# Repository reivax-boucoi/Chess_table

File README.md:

# Chess_table
Automated chess table with magnets &amp; CoreXY

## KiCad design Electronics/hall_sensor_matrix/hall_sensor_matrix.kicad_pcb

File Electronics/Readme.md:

# CNC Controller

### GRBL based controller running on Atmega328p and using A4988 stepper drivers.

Even though the chess board only requires 2 axis of motion (corexy platform), board has been developped with full 3 axis features.

Coolant, spindle, ... are brought out as 12V low-side switches (0.5A/1A). This is used to activate the electromagnet for the head.

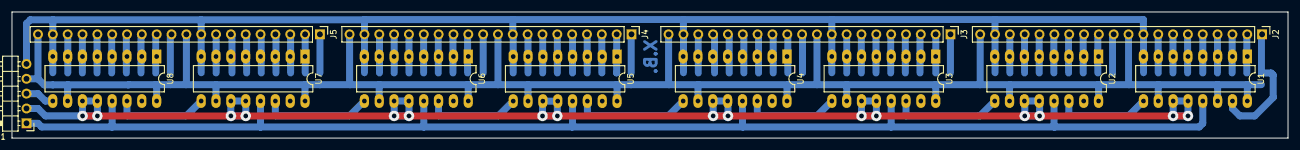
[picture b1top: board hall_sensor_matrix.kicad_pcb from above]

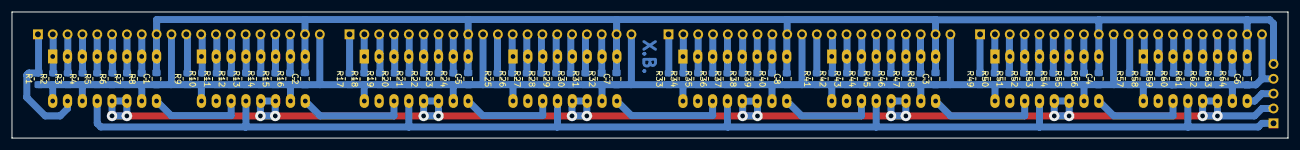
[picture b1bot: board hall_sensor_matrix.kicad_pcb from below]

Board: 2 copper layers, 218.4 x 21.6 mm, 85 parts (72 on the bottom side), 76 nets.

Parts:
C1, C2, C3, C4, C5, C6, C7: 100n; C_0805_2012Metric_Pad1.18x1.45mm_HandSolder
C8: 100n; R_0805_2012Metric_Pad1.20x1.40mm_HandSolder
J1: Conn_01x05; PinHeader_1x05_P2.54mm_Horizontal
J2, J3, J4, J5: Conn_01x20; PinHeader_1x20_P2.54mm_Vertical
R1, R2, R3, R4, R5, R6, R7, R8, R9, R10, R11, R12, R13, R14, R15, R16, R17, R18, R19, R20, R21, R22, R23, R24, R25, R26, R27, R28, R29, R30, R31, R32, R33, R34, R35, R36, R37, R38, R39, R40, R41, R42, R43, R44, R45, R46, R47, R48, R49, R50, R51, R52, R53, R54, R55, R56, R57, R58, R59, R60, R61, R62, R63, R64: R; R_0805_2012Metric_Pad1.20x1.40mm_HandSolder
U1, U2, U3, U4, U5, U6, U7, U8: 74LS597; DIP-16_W7.62mm_LongPads

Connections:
+5V: C1.1, C2.1, C3.1, C4.1, C5.1, C6.1, C7.1, C8.1, J1.4, J2.10, J2.20, J3.10, J3.20, J4.10, J4.20, J5.10, J5.20, R1.1, R2.1, R3.1, R4.1, R5.1, R6.1, R7.1, R8.1, R9.1, R10.1, R11.1, R12.1, R13.1, R14.1, R15.1, R16.1, R17.1, R18.1, R19.1, R20.1, R21.1, R22.1, R23.1, R24.1, R25.1, R26.1, R27.1, R28.1, R29.1, R30.1, R31.1, R32.1, R33.1, R34.1, R35.1, R36.1, R37.1, R38.1, R39.1, R40.1, R41.1, R42.1, R43.1, R44.1, R45.1, R46.1, R47.1, R48.1, R49.1, R50.1, R51.1, R52.1, R53.1, R54.1, R55.1, R56.1, R57.1, R58.1, R59.1, R60.1, R61.1, R62.1, R63.1, R64.1, U1.10 (~R), U1.14 (SER), U1.16 (VCC), U2.10 (~R), U2.16 (VCC), U3.10 (~R), U3.16 (VCC), U4.10 (~R), U4.16 (VCC), U5.10 (~R), U5.16 (VCC), U6.10 (~R), U6.16 (VCC), U7.10 (~R), U7.16 (VCC), U8.10 (~R), U8.16 (VCC)
/A1: J2.1, R1.2, U1.15 (A)
/A2: J2.2, R2.2, U1.1 (B)
/A3: J2.3, R3.2, U1.2 (C)
/A4: J2.4, R4.2, U1.3 (D)
/A5: J2.5, R5.2, U1.4 (E)
/A6: J2.6, R6.2, U1.5 (F)
/A7: J2.7, R7.2, U1.6 (G)
/A8: J2.8, R8.2, U1.7 (H)
/B1: J2.11, R9.2, U2.15 (A)
/B2: J2.12, R10.2, U2.1 (B)
/B3: J2.13, R11.2, U2.2 (C)
/B4: J2.14, R12.2, U2.3 (D)
/B5: J2.15, R13.2, U2.4 (E)
/B6: J2.16, R14.2, U2.5 (F)
/B7: J2.17, R15.2, U2.6 (G)
/B8: J2.18, R16.2, U2.7 (H)
/C1: J3.1, R17.2, U3.15 (A)
/C2: J3.2, R18.2, U3.1 (B)
/C3: J3.3, R19.2, U3.2 (C)
/C4: J3.4, R20.2, U3.3 (D)
/C5: J3.5, R21.2, U3.4 (E)
/C6: J3.6, R22.2, U3.5 (F)
/C7: J3.7, R23.2, U3.6 (G)
/C8: J3.8, R24.2, U3.7 (H)
/CLK: J1.2, U1.11 (SCK), U1.12 (CLK), U2.11 (SCK), U2.12 (CLK), U3.11 (SCK), U3.12 (CLK), U4.11 (SCK), U4.12 (CLK), U5.11 (SCK), U5.12 (CLK), U6.11 (SCK), U6.12 (CLK), U7.11 (SCK), U7.12 (CLK), U8.11 (SCK), U8.12 (CLK)
/D1: J3.11, R25.2, U4.15 (A)
/D2: J3.12, R26.2, U4.1 (B)
/D3: J3.13, R27.2, U4.2 (C)
/D4: J3.14, R28.2, U4.3 (D)
/D5: J3.15, R29.2, U4.4 (E)
/D6: J3.16, R30.2, U4.5 (F)
/D7: J3.17, R31.2, U4.6 (G)
/D8: J3.18, R32.2, U4.7 (H)
/Dout0: U1.9 (QH), U2.14 (SER)
/Dout1: U2.9 (QH), U3.14 (SER)
/Dout2: U3.9 (QH), U4.14 (SER)
/Dout3: U4.9 (QH), U5.14 (SER)
/Dout4: U5.9 (QH), U6.14 (SER)
/Dout5: U6.9 (QH), U7.14 (SER)
/Dout6: U7.9 (QH), U8.14 (SER)
/Dout7: J1.3, U8.9 (QH)
/E1: J4.1, R33.2, U5.15 (A)
/E2: J4.2, R34.2, U5.1 (B)
/E3: J4.3, R35.2, U5.2 (C)
/E4: J4.4, R36.2, U5.3 (D)
/E5: J4.5, R37.2, U5.4 (E)
/E6: J4.6, R38.2, U5.5 (F)
/E7: J4.7, R39.2, U5.6 (G)
/E8: J4.8, R40.2, U5.7 (H)
/F1: J4.11, R41.2, U6.15 (A)
/F2: J4.12, R42.2, U6.1 (B)
/F3: J4.13, R43.2, U6.2 (C)
/F4: J4.14, R44.2, U6.3 (D)
/F5: J4.15, R45.2, U6.4 (E)
/F6: J4.16, R46.2, U6.5 (F)
/F7: J4.17, R47.2, U6.6 (G)
/F8: J4.18, R48.2, U6.7 (H)
/G1: J5.1, R49.2, U7.15 (A)
/G2: J5.2, R50.2, U7.1 (B)
/G3: J5.3, R51.2, U7.2 (C)
/G4: J5.4, R52.2, U7.3 (D)
/G5: J5.5, R53.2, U7.4 (E)
/G6: J5.6, R54.2, U7.5 (F)
/G7: J5.7, R55.2, U7.6 (G)
/G8: J5.8, R56.2, U7.7 (H)
/H1: J5.11, R57.2, U8.15 (A)
/H2: J5.12, R58.2, U8.1 (B)
/H3: J5.13, R59.2, U8.2 (C)
/H4: J5.14, R60.2, U8.3 (D)
/H5: J5.15, R61.2, U8.4 (E)
/H6: J5.16, R62.2, U8.5 (F)
/H7: J5.17, R63.2, U8.6 (G)
/H8: J5.18, R64.2, U8.7 (H)
/Latch: J1.1, U1.13 (~SLoad), U2.13 (~SLoad), U3.13 (~SLoad), U4.13 (~SLoad), U5.13 (~SLoad), U6.13 (~SLoad), U7.13 (~SLoad), U8.13 (~SLoad)
GND: C1.2, C2.2, C3.2, C4.2, C5.2, C6.2, C7.2, C8.2, J1.5, J2.9, J2.19, J3.9, J3.19, J4.9, J4.19, J5.9, J5.19, U1.8 (GND), U2.8 (GND), U3.8 (GND), U4.8 (GND), U5.8 (GND), U6.8 (GND), U7.8 (GND), U8.8 (GND)

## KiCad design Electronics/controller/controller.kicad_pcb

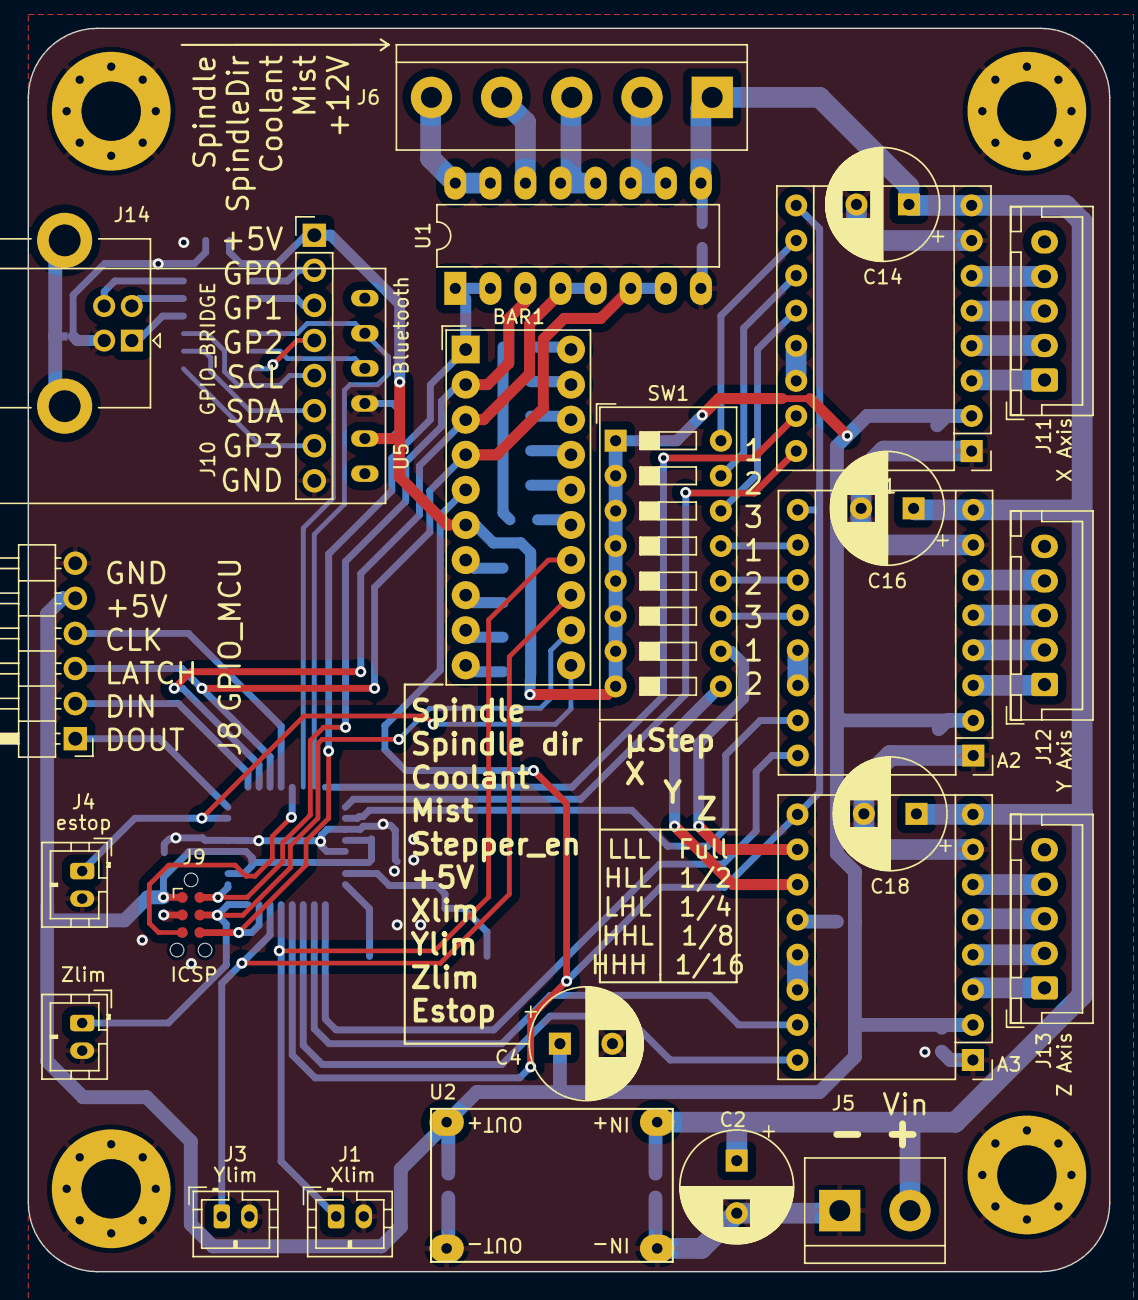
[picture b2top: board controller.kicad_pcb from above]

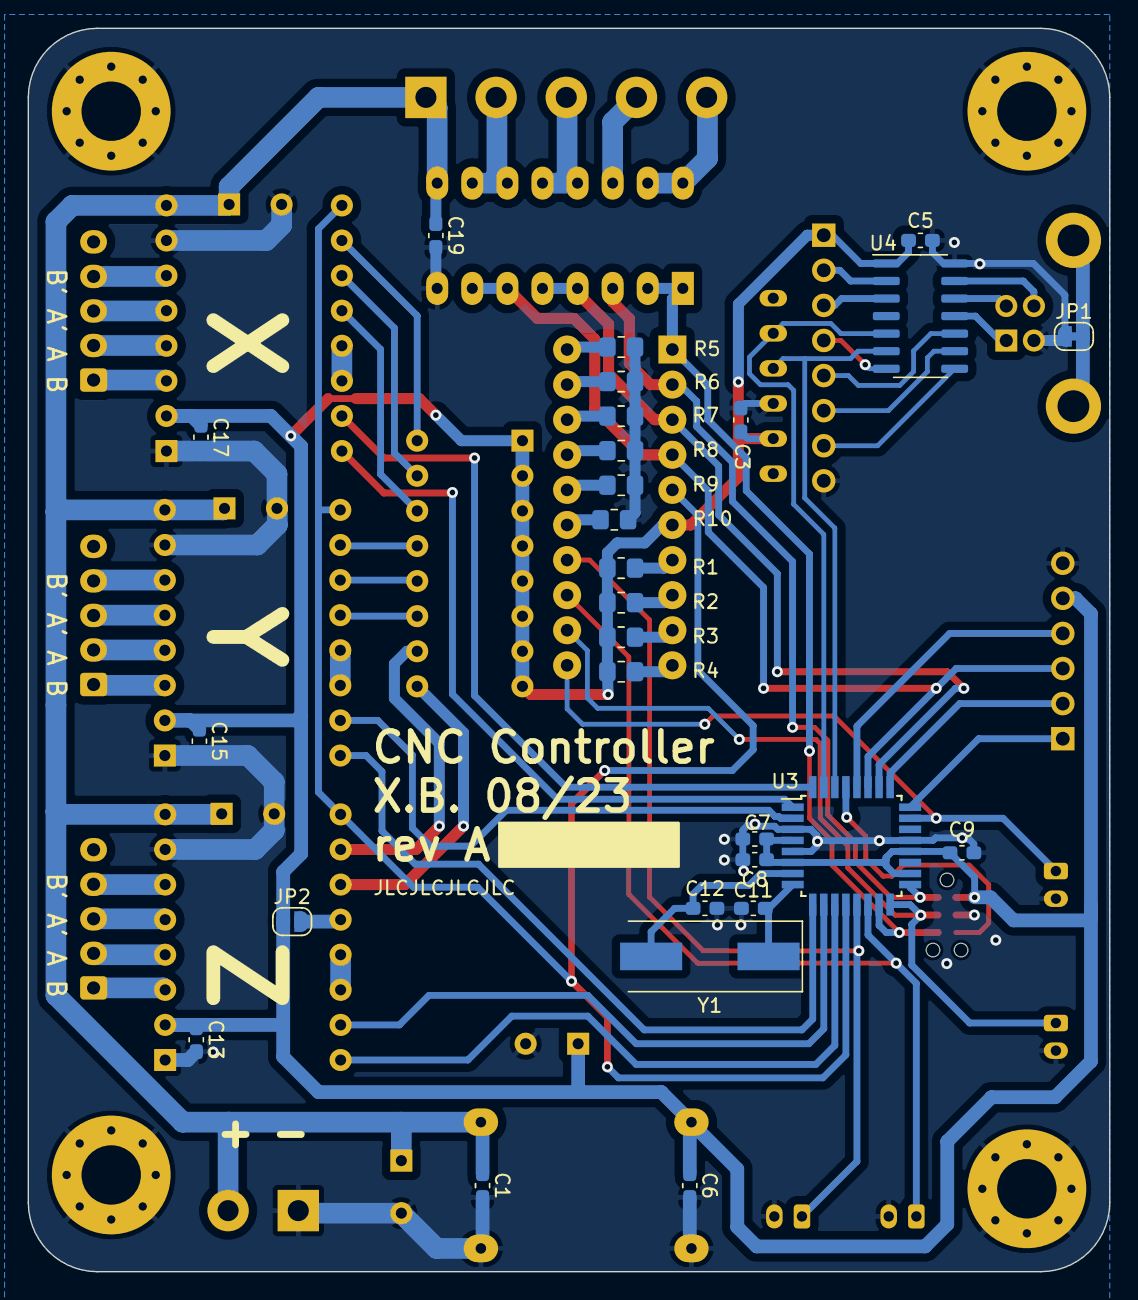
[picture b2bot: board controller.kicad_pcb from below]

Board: 2 copper layers, 78.3 x 90.0 mm, 58 parts (28 on the bottom side), 74 nets.

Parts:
A1, A2, A3: Pololu_Breakout_A4988; Pololu_Breakout-16_15.2x20.3mm
BAR1: HDSP-4830_2; HDSP-4830
C1, C3, C5, C6, C7, C8, C9, C13, C15, C17, C19: 100n; C_0603_1608Metric_Pad1.08x0.95mm_HandSolder
C2, C4, C14, C16, C18: 47u; CP_Radial_D8.0mm_P3.80mm
C11, C12: 22p; C_0603_1608Metric_Pad1.08x0.95mm_HandSolder
H1, H2, H3, H4: MountingHole_Pad; MountingHole_4.3mm_M4_Pad_Via
J1: Xlim; JST_PH_B2B-PH-K_1x02_P2.00mm_Vertical
J2: Zlim; JST_PH_B2B-PH-K_1x02_P2.00mm_Vertical
J3: Ylim; JST_PH_B2B-PH-K_1x02_P2.00mm_Vertical
J4: estop; JST_PH_B2B-PH-K_1x02_P2.00mm_Vertical
J5: Vin; TerminalBlock_bornier-2_P5.08mm
J6: Screw_Terminal_01x05; TerminalBlock_bornier-5_P5.08mm
J8: GPIO_MCU; PinHeader_1x06_P2.54mm_Horizontal
J9: ICSP; Tag-Connect_TC2030-IDC-NL_2x03_P1.27mm_Vertical
J10: GPIO_BRIDGE; PinHeader_1x08_P2.54mm_Vertical
J11: X Axis; JST_XH_B5B-XH-A_1x05_P2.50mm_Vertical
J12: Y Axis; JST_XH_B5B-XH-A_1x05_P2.50mm_Vertical
J13: Z Axis; JST_XH_B5B-XH-A_1x05_P2.50mm_Vertical
J14: USB_A; USB_B_Lumberg_2411_02_Horizontal
JP1: Jumper_2_Bridged; SolderJumper-2_P1.3mm_Bridged_RoundedPad1.0x1.5mm
JP2: Jumper_2_Open; SolderJumper-2_P1.3mm_Open_RoundedPad1.0x1.5mm
R1, R2, R3, R4, R5, R6, R7, R8, R9, R10: 1k; R_0805_2012Metric_Pad1.20x1.40mm_HandSolder
SW1: SW_DIP_x08; SW_DIP_SPSTx08_Slide_9.78x22.5mm_W7.62mm_P2.54mm
U1: ULN2003A; DIP-16_W7.62mm_LongPads
U2: Mini360; Mini360_step-down
U3: ATmega328P-A; TQFP-32_7x7mm_P0.8mm
U4: MCP2221AxSL; SOIC-14_3.9x8.7mm_P1.27mm
U5: Bluetooth; BlueSmirf
Y1: 16MHz; Crystal_SMD_HC49-SD

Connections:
+5V: A1.2 (VDD), A2.2 (VDD), A3.2 (VDD), BAR1.6 (A), C3.1, C4.1, C5.1, C6.1, C7.1, C8.1, C9.1, C13.1, C15.1, C17.1, J8.5, J9.1, J10.1, JP2.1 (A), R1.1, R2.1, R3.1, R4.1, SW1.1, SW1.2, SW1.3, SW1.4, SW1.5, SW1.6, SW1.7, SW1.8, U2.4 (OUT+), U3.4 (VCC), U3.6 (VCC), U3.18 (AVCC), U3.20 (AREF), U4.1 (VDD), U5.2 (VCC)
+12V: A1.8 (VMOT), A2.8 (VMOT), A3.8 (VMOT), C1.1, C2.1, C14.1, C16.1, C18.1, C19.1, J5.2, J6.1, U1.9 (COM), U2.2 (IN+)
/MCU/CLK: J8.4, U3.28 (PC5)
/MCU/DIN: J8.2, U3.25 (PC2)
/MCU/DOUT: J8.1, U3.24 (PC1)
/MCU/GP0: J10.2, U4.2 (GP0)
/MCU/GP1: J10.3, U4.3 (GP1)
/MCU/GP2: J10.4, U4.7 (GP2)
/MCU/GP3: J10.7, U4.8 (GP3)
/MCU/RX: U3.30 (PD0), U4.6 (UTx), U5.4 (TX)
/MCU/SCL: J10.5, U4.10 (SCL)
/MCU/SDA: J10.6, U4.9 (SDA)
/MCU/TX: U3.31 (PD1), U4.5 (URx), U5.5 (RX)
/MCU/VUSB: J14.1 (VBUS), U4.11 (VUSB)
/MCU/XTAL1: C12.1, U3.7 (XTAL1/PB6), Y1.2
/MCU/XTAL2: C11.1, U3.8 (XTAL2/PB7), Y1.1
/MCU/dirX: A1.16 (DIR), U3.1 (PD3)
/MCU/dirY: A2.16 (DIR), U3.9 (PD5)
/MCU/dirZ: A3.16 (DIR), U3.11 (PD7)
/MCU/stepX: A1.15 (STEP), U3.32 (PD2)
/MCU/stepY: A2.15 (STEP), U3.2 (PD4)
/MCU/stepZ: A3.15 (STEP), U3.10 (PD6)
/MCU/~RST: J9.5, U3.29 (~RESET/PC6)
/StepperDrivers/MS1_X: A1.10 (MS1), SW1.16
/StepperDrivers/MS1_Y: A2.10 (MS1), SW1.13
/StepperDrivers/MS1_Z: A3.10 (MS1), SW1.10
/StepperDrivers/MS2_X: A1.11 (MS2), SW1.15
/StepperDrivers/MS2_Y: A2.11 (MS2), SW1.12
/StepperDrivers/MS2_Z: A3.11 (MS2), SW1.9
/StepperDrivers/MS3_X: A1.12 (MS3), SW1.14
/StepperDrivers/MS3_Y: A2.12 (MS3), SW1.11
/StepperDrivers/MS3_Z: A3.12 (MS3), JP2.2 (B)
/coolant: BAR1.3 (A), U1.4 (I4), U1.5 (I5), U3.26 (PC3)
/estop: BAR1.11 (K), J4.1, U3.23 (PC0)
/mist: BAR1.4 (A), J8.3, U1.6 (I6), U1.7 (I7), U3.27 (PC4)
/spindle: BAR1.1 (A), J9.6, U1.1 (I1), U1.2 (I2), U3.15 (PB3)
/spindle_dir: BAR1.2 (A), J9.2, U1.3 (I3), U3.17 (PB5)
/stepper_enable: A1.9 (~ENABLE), A2.9 (~ENABLE), A3.9 (~ENABLE), BAR1.5 (A), U3.12 (PB0)
/xlim: BAR1.14 (K), J1.1, U3.13 (PB1)
/ylim: BAR1.13 (K), J3.1, U3.14 (PB2)
/zlim: BAR1.12 (K), J2.1, J9.4, U3.16 (PB4)
GND: A1.1 (GND), A1.7 (GND), A2.1 (GND), A2.7 (GND), A3.1 (GND), A3.7 (GND), C1.2, C2.2, C3.2, C4.2, C5.2, C6.2, C7.2, C8.2, C9.2, C11.2, C12.2, C13.2, C14.2, C15.2, C16.2, C17.2, C18.2, C19.2, H1.1, H2.1, H3.1, H4.1, J1.2, J2.2, J3.2, J4.2, J5.1, J8.6, J9.3, J10.8, J14.4 (GND), JP1.1 (A), R5.1, R6.1, R7.1, R8.1, R9.1, R10.1, U1.8 (GND), U2.1 (IN-), U2.3 (OUT-), U3.3 (GND), U3.5 (GND), U3.21 (GND), U4.14 (VSS), U5.3 (GND)
unnamed: A1.4 (1A), J11.2
unnamed: A1.3 (1B), J11.1
unnamed: A1.5 (2A), J11.3
unnamed: A1.6 (2B), J11.4
unnamed: A1.13 (~RESET), A1.14 (~SLEEP)
unnamed: A2.4 (1A), J12.2
unnamed: A2.3 (1B), J12.1
unnamed: A2.5 (2A), J12.3
unnamed: A2.6 (2B), J12.4
unnamed: A2.13 (~RESET), A2.14 (~SLEEP)
unnamed: A3.4 (1A), J13.2
unnamed: A3.3 (1B), J13.1
unnamed: A3.5 (2A), J13.3
unnamed: A3.6 (2B), J13.4
unnamed: A3.13 (~RESET), A3.14 (~SLEEP)
unnamed: BAR1.7 (A), R1.2
unnamed: BAR1.8 (A), R2.2
unnamed: BAR1.9 (A), R3.2
unnamed: BAR1.10 (A), R4.2
unnamed: BAR1.15 (K), R10.2
unnamed: BAR1.16 (K), R9.2
unnamed: BAR1.17 (K), R8.2
unnamed: BAR1.18 (K), R7.2
unnamed: BAR1.19 (K), R6.2
unnamed: BAR1.20 (K), R5.2
unnamed: J6.2, U1.10 (O7), U1.11 (O6)
unnamed: J6.3, U1.12 (O5), U1.13 (O4)
unnamed: J6.4, U1.14 (O3)
unnamed: J6.5, U1.15 (O2), U1.16 (O1)
unnamed: J14.3 (D+), U4.13 (D+)
unnamed: J14.2 (D-), U4.12 (D-)
unnamed: J14.5 (Shield), JP1.2 (B)

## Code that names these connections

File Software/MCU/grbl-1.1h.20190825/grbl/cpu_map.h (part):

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  #define LIMIT_PORT       PORTB
  #define X_LIMIT_BIT      1  // Uno Digital Pin 9
  #define Y_LIMIT_BIT      2  // Uno Digital Pin 10
  #ifdef VARIABLE_SPINDLE // Z Limit pin and spindle enabled swapped to access hardware PWM on Pin 11.
    #define Z_LIMIT_BIT	   4 // Uno Digital Pin 12
  #else
    #define Z_LIMIT_BIT    3  // Uno Digital Pin 11
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
  #if !defined(ENABLE_DUAL_AXIS)

    // Define flood and mist coolant enable output pins.
    #define COOLANT_FLOOD_DDR   DDRC
    #define COOLANT_FLOOD_PORT  PORTC
    #define COOLANT_FLOOD_BIT   3  // Uno Analog Pin 3
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    #define COOLANT_MIST_PORT  PORTC
    #define COOLANT_MIST_BIT   4  // Uno Analog Pin 4

    // Define spindle enable and spindle direction output pins.
    #define SPINDLE_ENABLE_DDR    DDRB
    #define SPINDLE_ENABLE_PORT   PORTB
    // Z Limit pin and spindle PWM/enable pin swapped to access hardware PWM on Pin 11.
    #ifdef VARIABLE_SPINDLE
      #ifdef USE_SPINDLE_DIR_AS_ENABLE_PIN
        // If enabled, spindle direction pin now used as spindle enable, while PWM remains on D11.
        #define SPINDLE_ENABLE_BIT    5  // Uno Digital Pin 13 (NOTE: D13 can't be pulled-high input due to LED.)
      #else
        #define SPINDLE_ENABLE_BIT    3  // Uno Digital Pin 11
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      #define SPINDLE_DIRECTION_BIT   5  // Uno Digital Pin 13 (NOTE: D13 can't be pulled-high input due to LED.)
    #endif

    // Variable spindle configuration below. Do not change unless you know what you are doing.
    // NOTE: Only used when variable spindle is enabled.
    #define SPINDLE_PWM_MAX_VALUE     255 // Don't change. 328p fast PWM mode fixes top value as 255.
    #ifndef SPINDLE_PWM_MIN_VALUE
      #define SPINDLE_PWM_MIN_VALUE   1   // Must be greater than zero.
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
    // Dual axis feature requires an independent step pulse pin to operate. The independent direction pin is not 
    // absolutely necessary but facilitates easy direction inverting with a Grbl $$ setting. These pins replace 
    // the spindle direction and optional coolant mist pins.

    #ifdef DUAL_AXIS_CONFIG_PROTONEER_V3_51
      // NOTE: Step pulse and direction pins may be on any port and output pin.
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      #define DUAL_LIMIT_BIT    Z_LIMIT_BIT
      #define LIMIT_MASK        ((1<<X_LIMIT_BIT)|(1<<Y_LIMIT_BIT)|(1<<Z_LIMIT_BIT)|(1<<DUAL_LIMIT_BIT))

      // Define coolant enable output pins.
      // NOTE: Coolant flood moved from A3 to A4. Coolant mist not supported with dual axis feature on Arduino Uno.
      #define COOLANT_FLOOD_DDR   DDRB
      #define COOLANT_FLOOD_PORT  PORTB
      #define COOLANT_FLOOD_BIT   5  // Uno Digital Pin 13

      // Define spindle enable output pin.
      // NOTE: Spindle enable moved from D12 to A3 (old coolant flood enable pin). Spindle direction pin is removed.
      #define SPINDLE_ENABLE_DDR    DDRB
      #define SPINDLE_ENABLE_PORT   PORTB
      #ifdef VARIABLE_SPINDLE
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        #define SPINDLE_ENABLE_BIT    4  // Uno Digital Pin 12
      #endif

      // Variable spindle configuration below. Do not change unless you know what you are doing.
      // NOTE: Only used when variable spindle is enabled.
      #define SPINDLE_PWM_MAX_VALUE     255 // Don't change. 328p fast PWM mode fixes top value as 255.
      #ifndef SPINDLE_PWM_MIN_VALUE
        #define SPINDLE_PWM_MIN_VALUE   1   // Must be greater than zero.
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      #define SPINDLE_PWM_BIT   3    // Uno Digital Pin 11
    #endif

    // NOTE: Variable spindle not supported with this shield.
    #ifdef DUAL_AXIS_CONFIG_CNC_SHIELD_CLONE
      // NOTE: Step pulse and direction pins may be on any port and output pin.
      #define STEP_DDR_DUAL       DDRB
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      #define DUAL_LIMIT_BIT    Z_LIMIT_BIT
      #define LIMIT_MASK        ((1<<X_LIMIT_BIT)|(1<<Y_LIMIT_BIT)|(1<<Z_LIMIT_BIT)|(1<<DUAL_LIMIT_BIT))

      // Define coolant enable output pins.
      // NOTE: Coolant flood moved from A3 to A4. Coolant mist not supported with dual axis feature on Arduino Uno.
      #define COOLANT_FLOOD_DDR   DDRC
      #define COOLANT_FLOOD_PORT  PORTC
      #define COOLANT_FLOOD_BIT   4  // Uno Analog Pin 4

      // Define spindle enable output pin.
      // NOTE: Spindle enable moved from D12 to A3 (old coolant flood enable pin). Spindle direction pin is removed.
      #define SPINDLE_ENABLE_DDR    DDRC
      #define SPINDLE_ENABLE_PORT   PORTC
      #define SPINDLE_ENABLE_BIT    3  // Uno Analog Pin 3
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
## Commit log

2023-08-26 added driver board
2023-08-26 added early mechanicals
2023-08-26 revamp
2023-08-26 added board pics
2023-08-26 added board gerbers
2023-08-26 updated gitignore
2023-08-26 added readme
2023-08-27 added first nodejs server test
2023-08-28 added custome grbl
2023-08-29 updated custom grbl
2023-08-29 added makefile
2023-08-29 added make
2023-08-31 updated reporting to 4bit width
2023-09-01 added brd png
2023-09-01 added hall piso brd
2023-09-02 added stl models
2023-10-04 added content
2023-11-18 added svg viz

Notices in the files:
Software/MCU/grbl-1.1h.20190825/grbl/cpu_map.h:
Copyright (c) 2012-2016 Sungeun K. Jeon for Gnea Research LLC
Grbl is free software: you can redistribute it and/or modify
it under the terms of the GNU General Public License as published by
the Free Software Foundation, either version 3 of the License, or
(at your option) any later version.
